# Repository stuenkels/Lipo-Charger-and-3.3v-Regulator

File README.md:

# Lipo-Charger-and-3.3v-Regulator
Lipo battery charger with 3.3v fixed output. TP4056 IC used for charging. DWO1-A IC for battery protection, combined with the FS8205A dule mosfett chip. TPS63001 IC for fixed voltage regulation.

## 3d View

## Finished board

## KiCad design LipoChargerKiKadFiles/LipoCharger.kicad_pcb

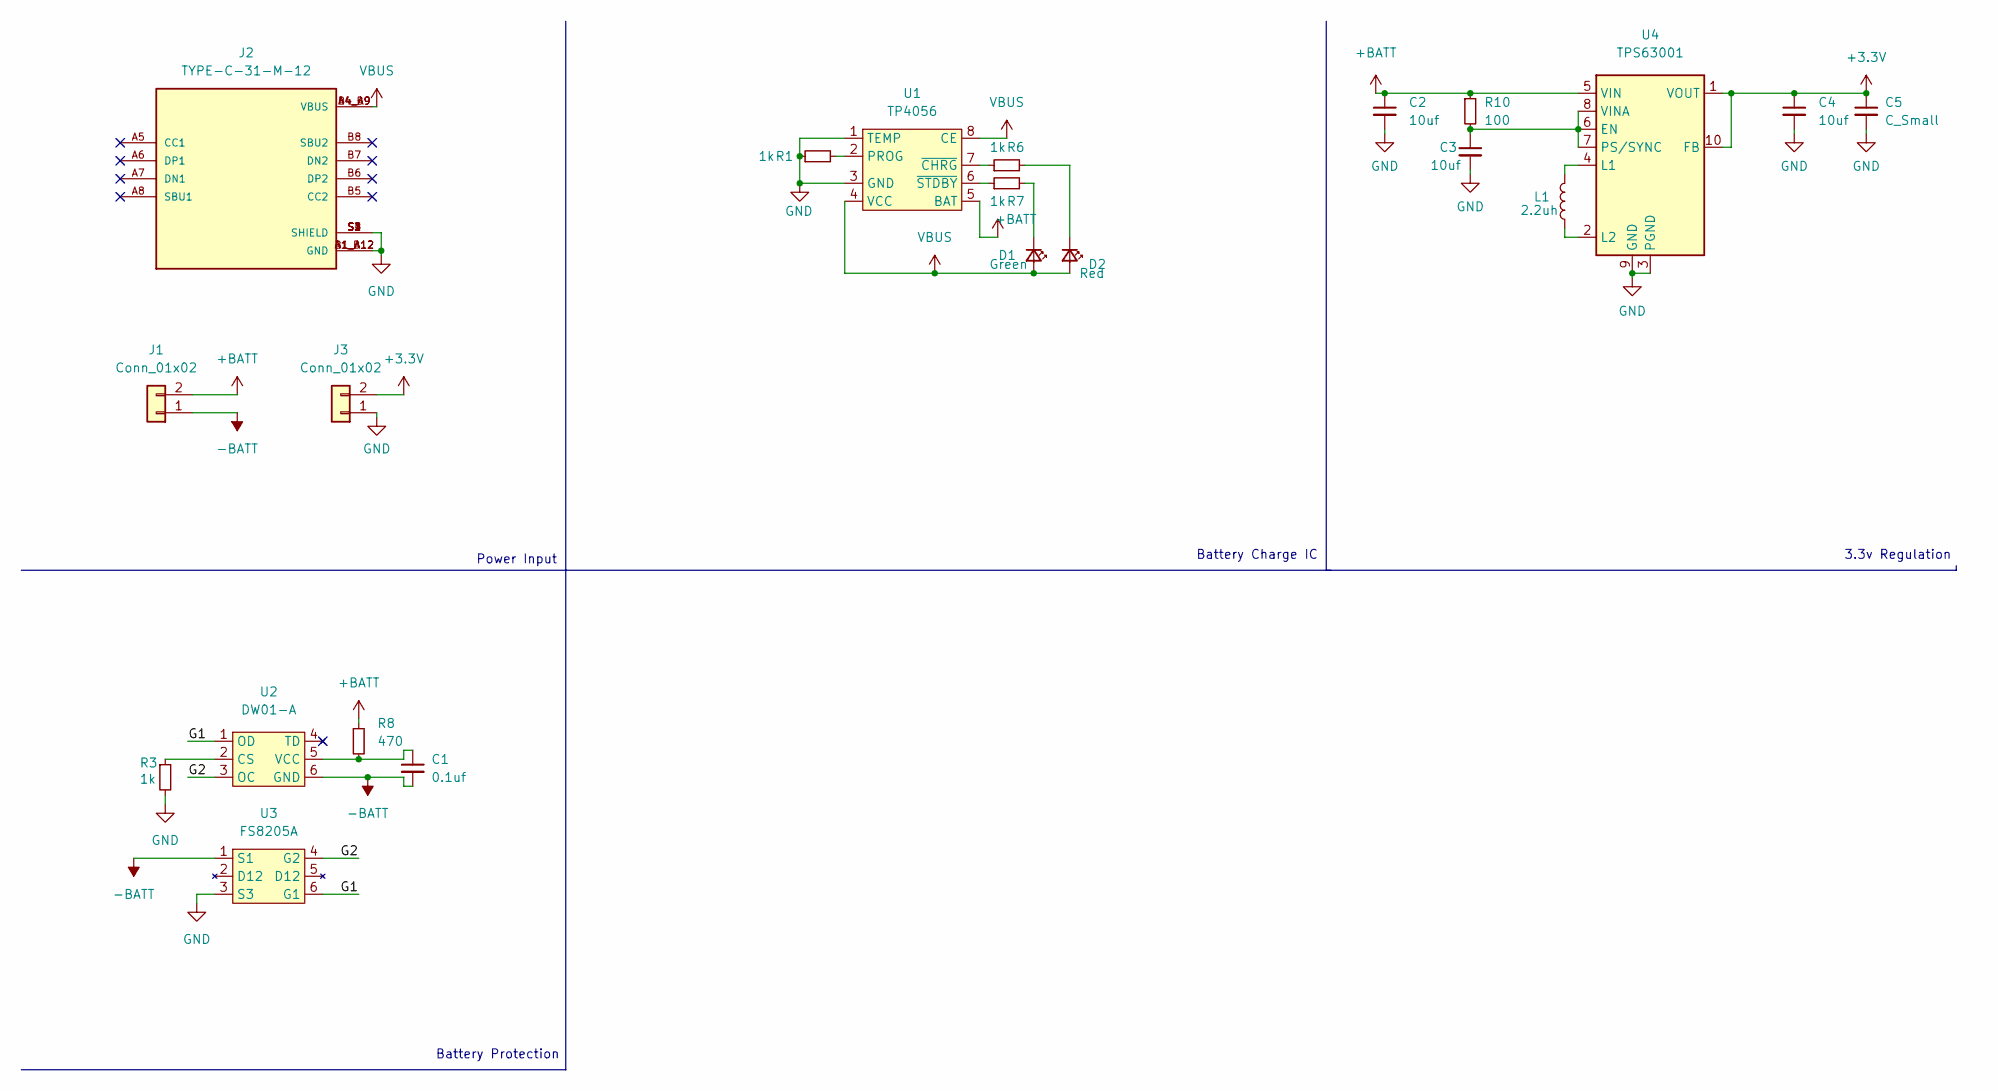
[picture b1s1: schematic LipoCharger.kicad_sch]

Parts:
C1: 0.1uf; C_0805_2012Metric
C2, C3, C4: 10uf; C_0805_2012Metric
C5: C_Small; C_0805_2012Metric
D1: Green; LED_0805_2012Metric
D2: Red; LED_0805_2012Metric
J1, J3: Conn_01x02; PinHeader_1x02_P2.54mm_Vertical
J2: TYPE-C-31-M-12; HRO_TYPE-C-31-M-12; PARTREV 2020.12.08
L1: 2.2uh; L_1210_3225Metric
R1, R3, R6, R7: 1k; R_0805_2012Metric
R8: 470; R_0805_2012Metric
R10: 100; R_0805_2012Metric
U1: TP4056
U2: DW01-A; SOT-23-6
U3: FS8205A; SOT-23-6
U4: TPS63001; Texas_DRC0010J_ThermalVias

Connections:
+3.3V: C4.1, C5.1, J3.2, U4.1 (VOUT), U4.10 (FB)
+BATT: C2.1, J1.2, R8.1, R10.1, U1.5 (BAT), U4.5 (VIN)
-BATT: C1.2, J1.1, U2.6 (GND), U3.1 (S1)
/G1: U2.1 (OD), U3.6 (G1)
/G2: U2.3 (OC), U3.4 (G2)
GND: C2.2, C3.2, C4.2, C5.2, J2.A1_B12 (GND), J2.B1_A12 (GND), J2.S1 (SHIELD), J2.S2 (SHIELD), J2.S3 (SHIELD), J2.S4 (SHIELD), J3.1, R1.1, R3.2, U1.1 (TEMP), U1.3 (GND), U3.3 (S3), U4.3 (PGND), U4.9 (GND), U4.11 (PGND)
unnamed: C1.1, R8.2, U2.5 (VCC)
unnamed: C3.1, R10.2, U4.6 (EN), U4.7 (PS/SYNC), U4.8 (VINA)
unnamed: D1.1 (K), R7.2
unnamed: D2.1 (K), R6.2
unnamed: L1.1, U4.2 (L2)
unnamed: L1.2, U4.4 (L1)
unnamed: R1.2, U1.2 (PROG)
unnamed: R3.1, U2.2 (CS)
unnamed: R6.1, U1.7 (~CHRG)
unnamed: R7.1, U1.6 (~STDBY)
VBUS: D1.2 (A), D2.2 (A), J2.A4_B9 (VBUS), J2.B4_A9 (VBUS), U1.4 (VCC), U1.8 (CE)

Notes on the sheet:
Battery Protection
Power Input
Battery Charge IC
3.3v Regulation

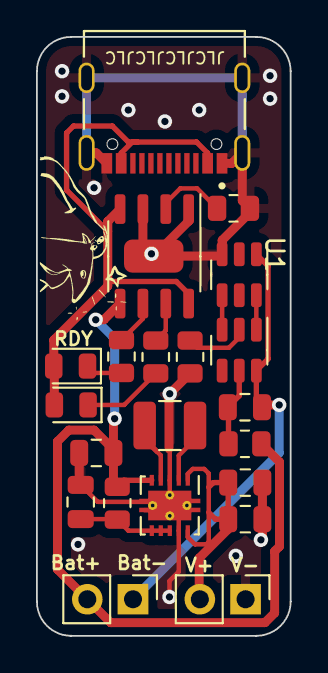
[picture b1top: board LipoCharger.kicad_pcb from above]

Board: 2 copper layers, 14.1 x 33.3 mm, 21 parts (0 on the bottom side), 17 nets.

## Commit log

2024-03-19 test
2024-03-19 initial file upload
2024-03-20 gerber and images
2024-03-20 fixed readme
2024-03-20 fixed typo
